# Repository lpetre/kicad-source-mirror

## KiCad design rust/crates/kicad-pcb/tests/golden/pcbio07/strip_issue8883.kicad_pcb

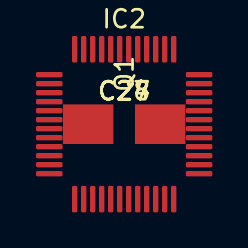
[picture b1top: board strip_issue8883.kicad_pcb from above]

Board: 2 copper layers, 5 parts (0 on the bottom side), 6 nets, no tracks yet.

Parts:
C24: 100nF; C_1206_3216Metric
C27, C28: 18pF; C_1206_3216Metric
IC2: STM32G491CET6; LQFP-48_7x7mm_P0.5mm
Q1: QC5CB10.000; Crystal_SMD_5032-2Pin_5.0x3.2mm_IBF

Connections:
+3V3: IC2.1 (Vbat), IC2.24 (Vdd), IC2.36 (Vdd), IC2.48 (Vdd)
GND: C24.2, C27.2, C28.2, IC2.23 (VSS/GND), IC2.35 (VSS/GND), IC2.47 (VSS/GND)
unnamed: C27.1, IC2.5 (PF0_OSC), Q1.2
unnamed: C28.1, IC2.6 (PF1_OSC), Q1.1
unnamed: IC2.20 (VRef+), IC2.21 (Vdda)
~RESET: C24.1, IC2.7 (PG10_~RES)
